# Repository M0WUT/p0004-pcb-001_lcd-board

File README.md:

# P0004-PCB-001 - LCD Board
Front panel board featuring MCU and LCD

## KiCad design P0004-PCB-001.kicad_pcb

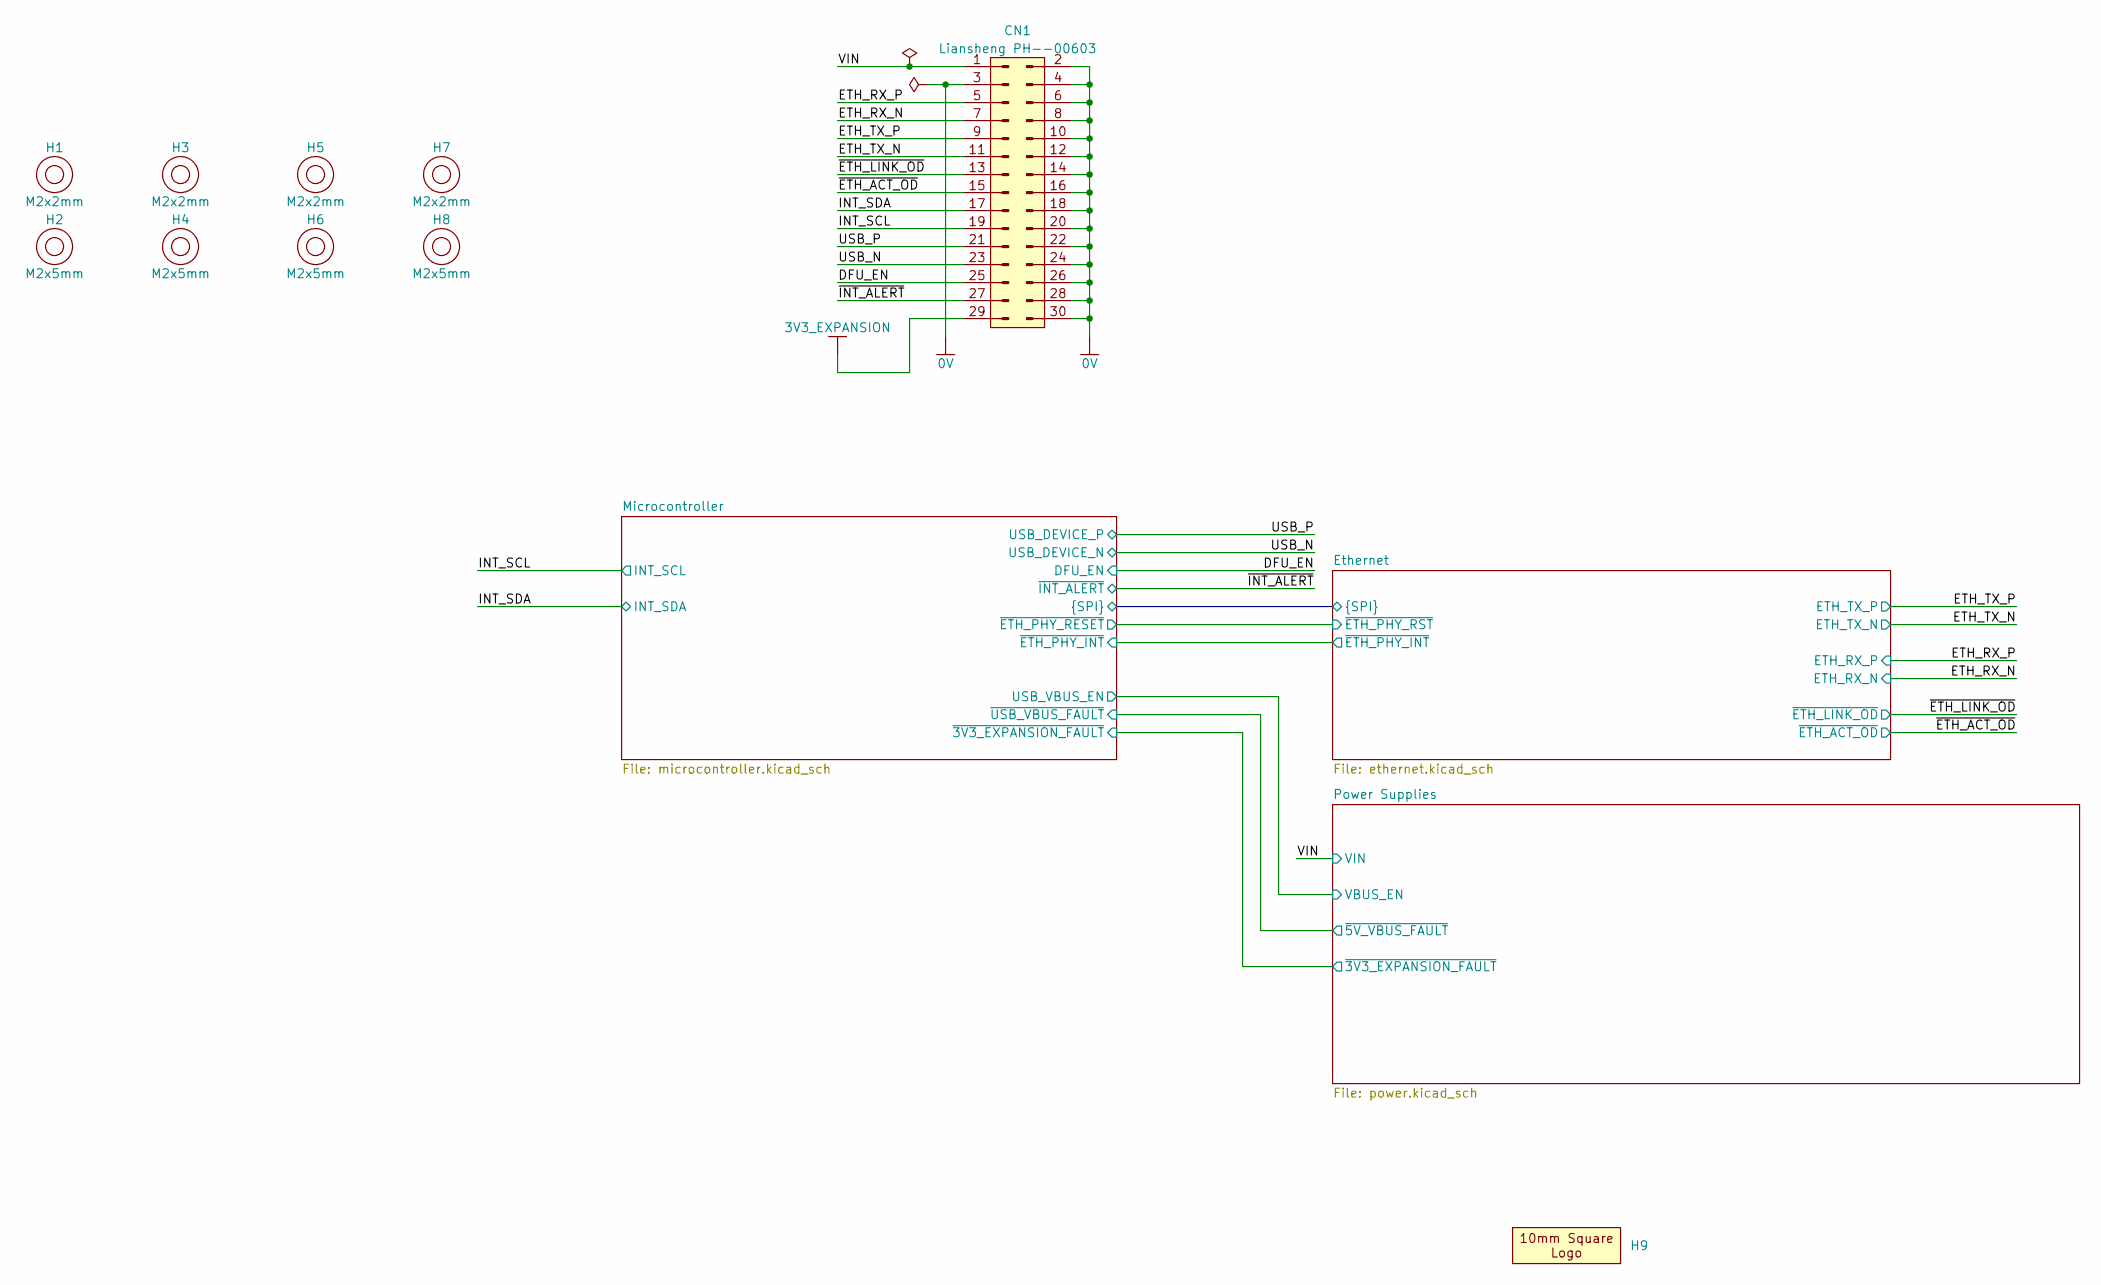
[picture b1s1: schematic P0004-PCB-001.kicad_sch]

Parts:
CN1: Liansheng PH--00603; Liansheng_PH--00603; MPN PH--00603; JLC Part Number C2685170
H1, H3, H5, H7: M2x2mm; Accu_HPS-4-2.2-2-POM-BL; MPN HPS-4-2.2-2-POM-BL
H2, H4, H6, H8: M2x5mm; Accu_HPS-4-2.2-5-POM-BL; MPN HPS-4-2.2-2-POM-BL
H9: Logo_10mmx10mm

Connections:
0V: CN1.2 (Pin_1), CN1.3, CN1.4, CN1.6, CN1.8, CN1.10, CN1.12, CN1.14, CN1.16, CN1.18, CN1.20, CN1.22, CN1.24, CN1.26, CN1.28, CN1.30; also elsewhere on the board
3V3_EXPANSION: CN1.29; also elsewhere on the board
/DFU_EN: CN1.25; also elsewhere on the board
/ETH_RX_N: CN1.7; also elsewhere on the board
/ETH_RX_P: CN1.5; also elsewhere on the board
/ETH_TX_N: CN1.11; also elsewhere on the board
/ETH_TX_P: CN1.9; also elsewhere on the board
/INT_SCL: CN1.19; also elsewhere on the board
/INT_SDA: CN1.17; also elsewhere on the board
/USB_N: CN1.23; also elsewhere on the board
/USB_P: CN1.21; also elsewhere on the board
/VIN: CN1.1; also elsewhere on the board
/~ETH_ACT_OD: CN1.15; also elsewhere on the board
/~ETH_LINK_OD: CN1.13; also elsewhere on the board
/~INT_ALERT: CN1.27; also elsewhere on the board

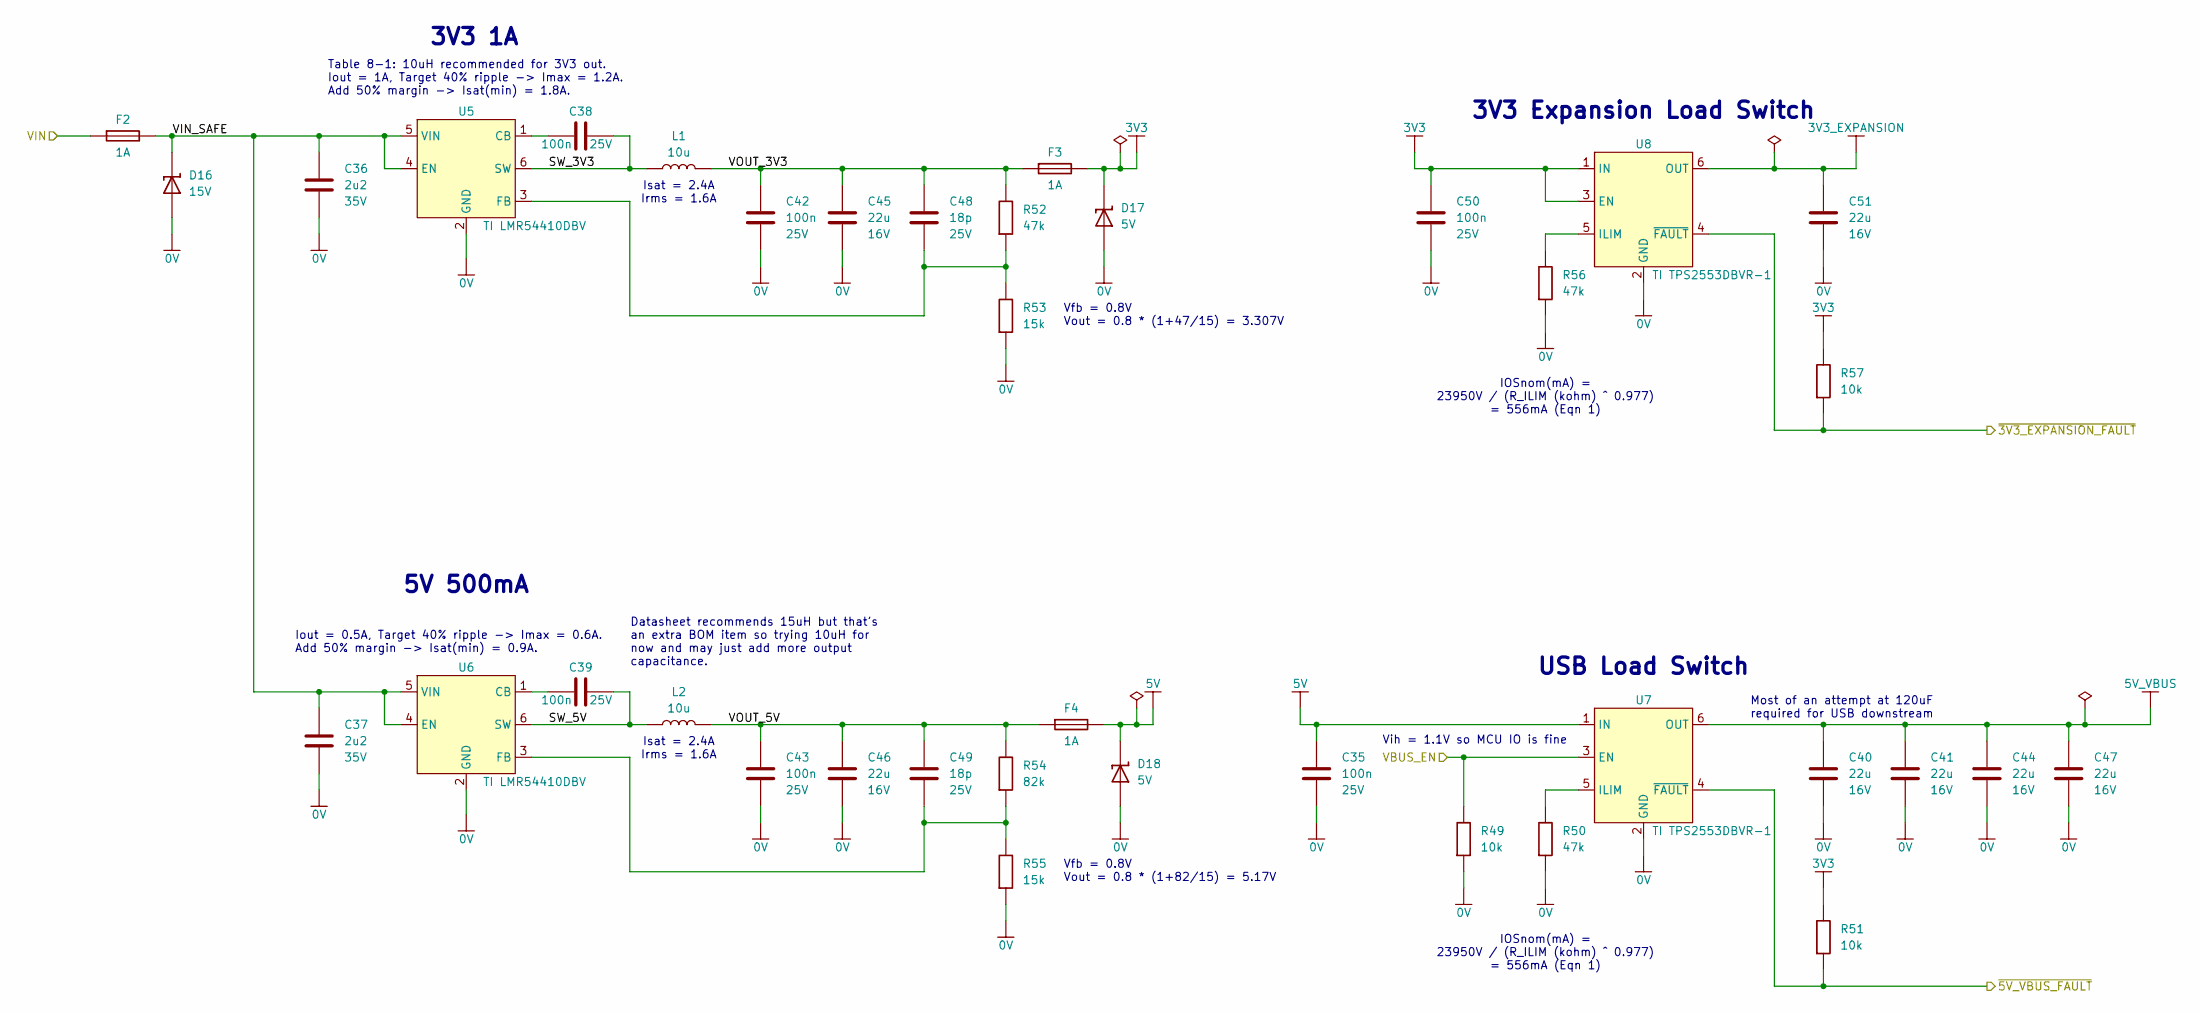
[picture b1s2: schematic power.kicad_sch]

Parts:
C35, C38, C39, C42, C43, C50: 100n; C_0402_1005Metric; Voltage 25V; Tolerance 10%; MPN CC0402KRX7R8BB104
C36, C37: 2u2; C_0402_1005Metric; Voltage 35V; Tolerance 10%; MPN GRM155R6YA225KE11
C40, C41, C44, C45, C46, C47, C51: 22u; C_0603_1608Metric; Voltage 16V; Tolerance 20%; MPN GRM188R61C226ME01
C48, C49: 18p; C_0402_1005Metric; Voltage 25V; Tolerance 10%; MPN C0402C180K3GACTU
D16: 15V; D_SOD-323; MPN CDSOD-323-T15S
D17, D18: 5V; D_SOD-523; MPN H5VND5U
F2, F3, F4: 1A; Fuse_0603_1608Metric; MPN 0467001.NR
L1, L2: 10u; APV_ANR4030; Tolerance 20%; MPN ANR4030T100M
R49, R51, R57: 10k; R_0402_1005Metric; Tolerance 1%; MPN RK73H1ETTP1002F
R50, R52, R56: 47k; R_0402_1005Metric; Tolerance 1%; MPN RK73H1ETTP4702F
R53, R55: 15k; R_0402_1005Metric; Tolerance 1%; MPN RK73H1ETTP1502F
R54: 82k; R_0402_1005Metric; Tolerance 1%; MPN RK73H1ETTP8202F
U5, U6: TI LMR54410DBV; SOT-23-6; MPN LMR54410DBV; JLCPCB Order # C3200265
U7, U8: TI TPS2553DBVR-1; SOT-23-6; MPN TPS2553DBVR-1; JLCPCB Order # C55266

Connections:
0V: C35.2, C36.2, C37.2, C40.2, C41.2, C42.2, C43.2, C44.2, C45.2, C46.2, C47.2, C50.2, C51.2, D16.2 (A), D17.2 (A), D18.2 (A), R49.2, R50.2, R53.2, R55.2, R56.2, U5.2 (GND), U6.2 (GND), U7.2 (GND), U8.2 (GND); also elsewhere on the board
3V3: C50.1, D17.1 (K), F3.2, R51.1, R57.1, U8.1 (IN), U8.3 (EN); also elsewhere on the board
3V3_EXPANSION: C51.1, U8.6 (OUT); also elsewhere on the board
5V: C35.1, D18.1 (K), F4.2, U7.1 (IN)
5V_VBUS: C40.1, C41.1, C44.1, C47.1, U7.6 (OUT); also elsewhere on the board
/Microcontroller/USB_VBUS_EN: R49.1, U7.3 (EN); also elsewhere on the board
/Microcontroller/~3V3_EXPANSION_FAULT: R57.2, U8.4 (~FAULT); also elsewhere on the board
/Microcontroller/~USB_VBUS_FAULT: R51.2, U7.4 (~FAULT); also elsewhere on the board
/Power Supplies/SW_3V3: C38.1, L1.1, U5.6 (SW)
/Power Supplies/SW_5V: C39.1, L2.1, U6.6 (SW)
/Power Supplies/VIN_SAFE: C36.1, C37.1, D16.1 (K), F2.2, U5.4 (EN), U5.5 (VIN), U6.4 (EN), U6.5 (VIN)
/Power Supplies/VOUT_3V3: C42.1, C45.1, C48.1, F3.1, L1.2, R52.1
/Power Supplies/VOUT_5V: C43.1, C46.1, C49.1, F4.1, L2.2, R54.1
/VIN: F2.1; also elsewhere on the board
unnamed: C38.2, U5.1 (CB)
unnamed: C48.2, R52.2, R53.1, U5.3 (FB)
unnamed: C39.2, U6.1 (CB)
unnamed: C49.2, R54.2, R55.1, U6.3 (FB)
unnamed: R50.1, U7.5 (ILIM)
unnamed: R56.1, U8.5 (ILIM)

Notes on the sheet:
3V3 1A
Isat = 2.4A Irms = 1.6A
IOSnom(mA) = 23950V / (R_ILIM (kohm) ^ 0.977) = 556mA (Eqn 1)
Vfb = 0.8V Vout = 0.8 * (1+82/15) = 5.17V
Vih = 1.1V so MCU IO is fine
Table 8-1: 10uH recommended for 3V3 out. Iout = 1A, Target 40% ripple -> Imax = 1.2A. Add 50% margin -> Isat(min) = 1.8A.
USB Load Switch
Most of an attempt at 120uF required for USB downstream
3V3 Expansion Load Switch
Vfb = 0.8V Vout = 0.8 * (1+47/15) = 3.307V
5V 500mA
Datasheet recommends 15uH but that's an extra BOM item so trying 10uH for now and may just add more output capacitance.
Iout = 0.5A, Target 40% ripple -> Imax = 0.6A. Add 50% margin -> Isat(min) = 0.9A.

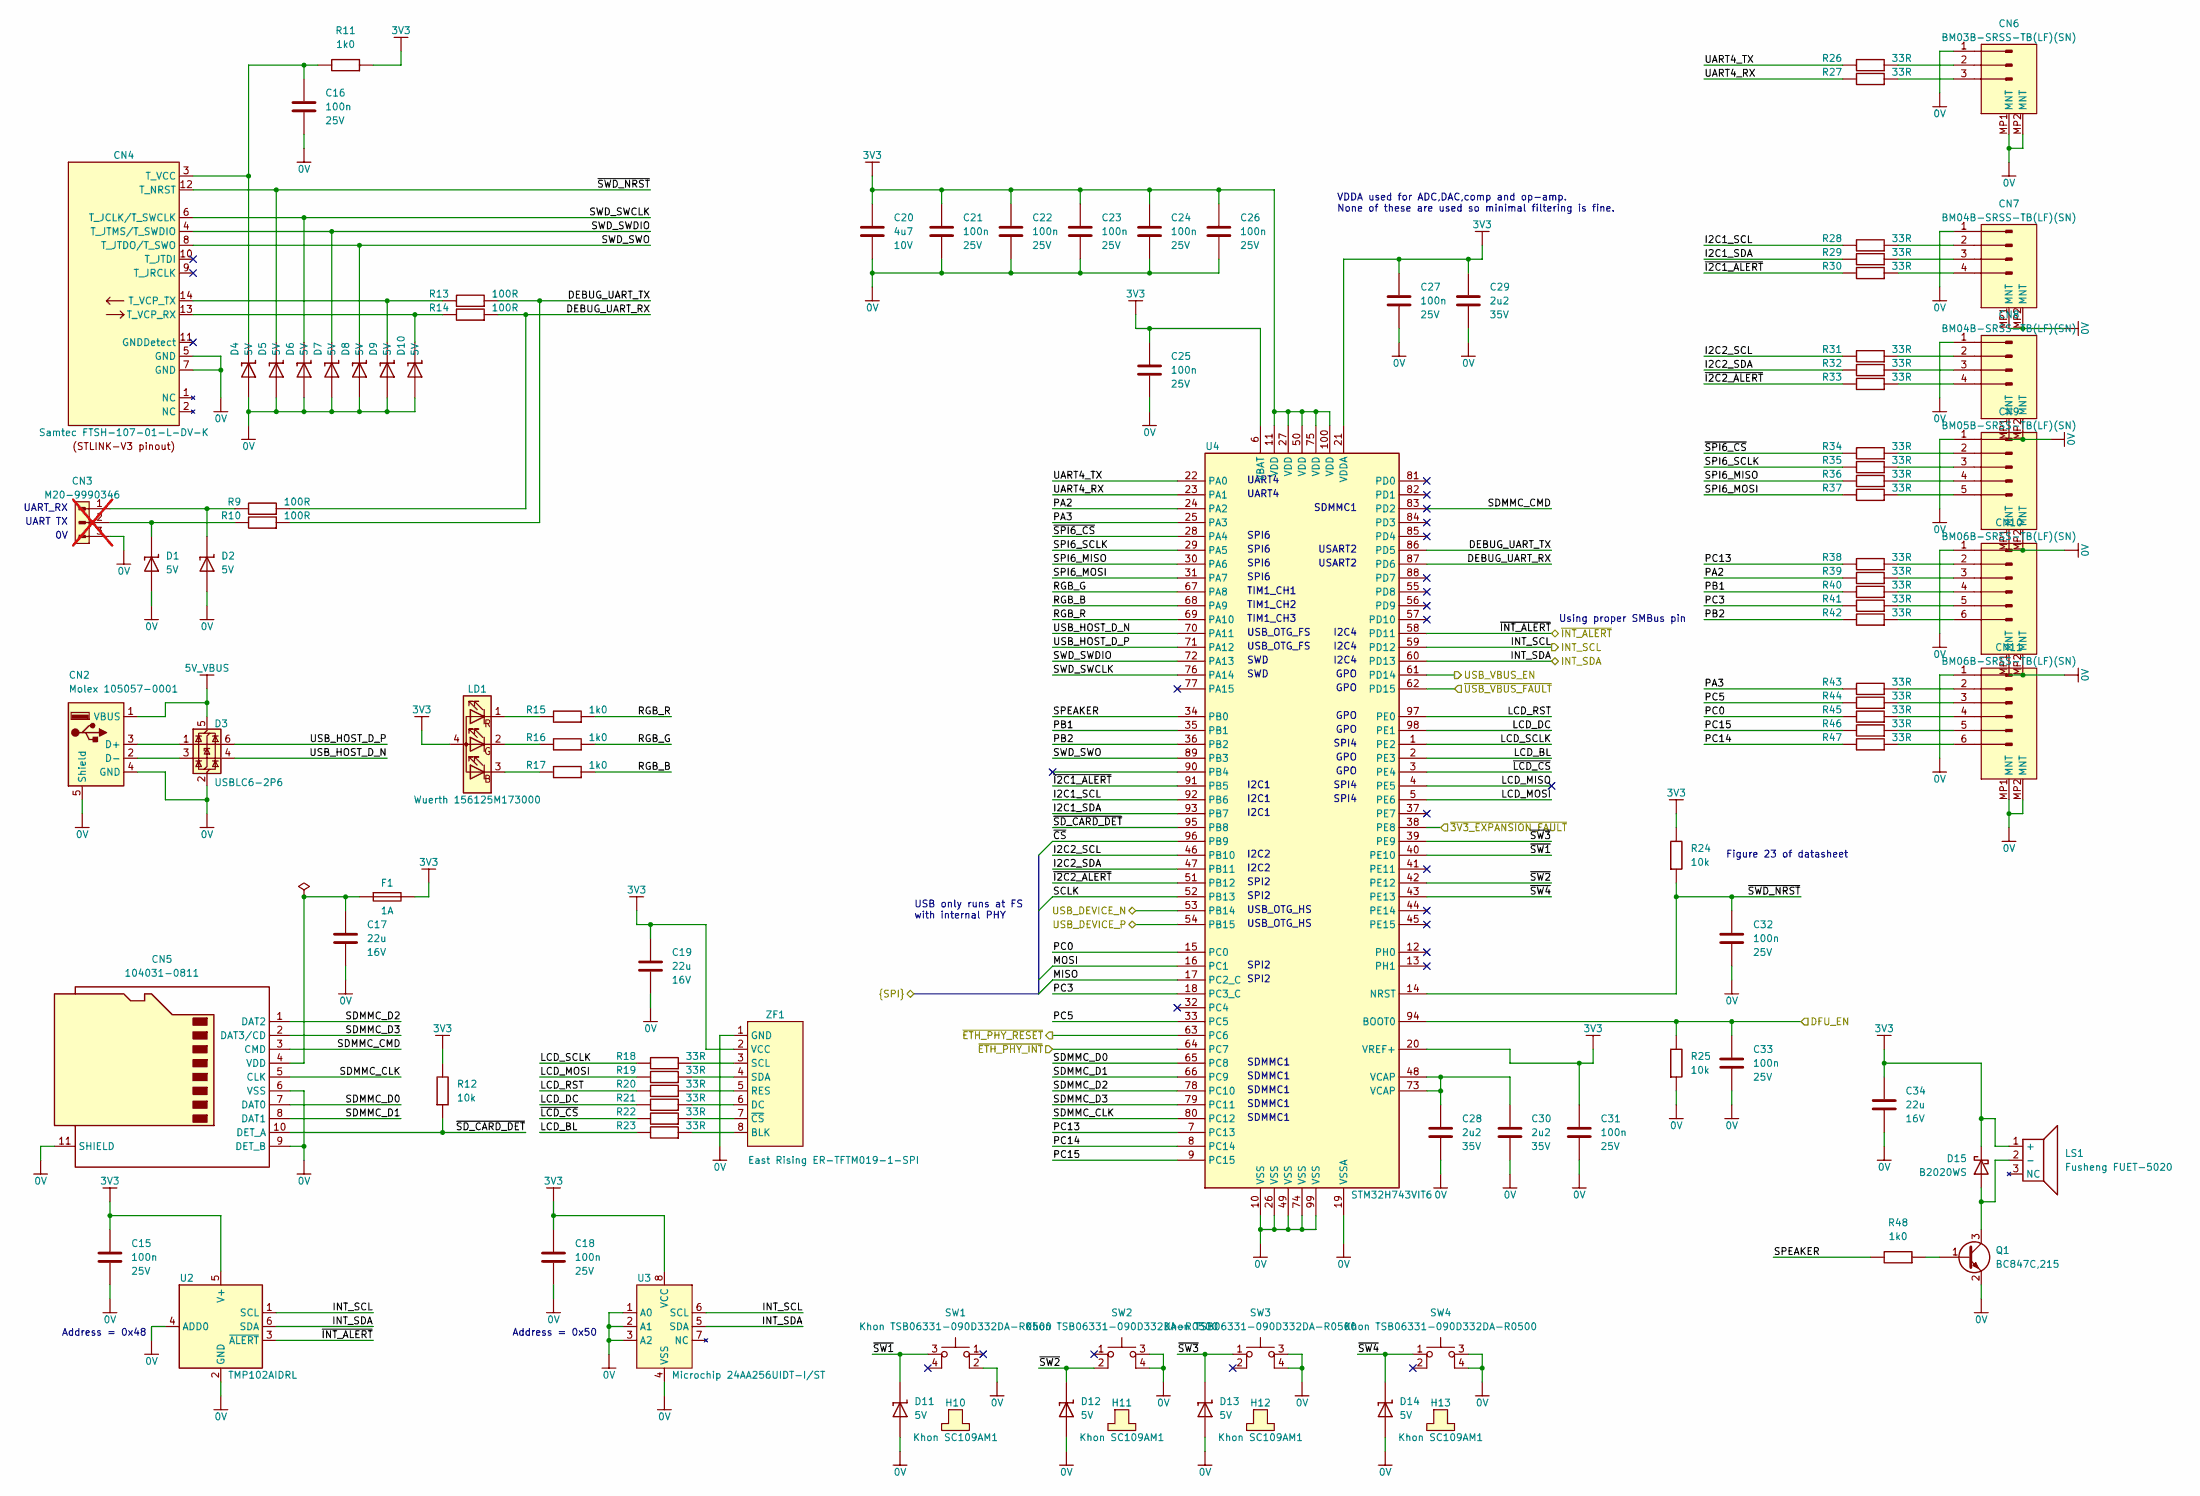
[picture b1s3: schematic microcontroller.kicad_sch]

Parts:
C15, C16, C18, C21, C22, C23, C24, C25, C26, C27, C31, C32, C33: 100n; C_0402_1005Metric; Voltage 25V; Tolerance 10%; MPN CC0402KRX7R8BB104
C17, C19, C34: 22u; C_0603_1608Metric; Voltage 16V; Tolerance 20%; MPN GRM188R61C226ME01
C20: 4u7; C_0402_1005Metric; Voltage 10V; Tolerance 20%; MPN GRM155D71A475ME15
C28, C29, C30: 2u2; C_0402_1005Metric; Voltage 35V; Tolerance 10%; MPN GRM155R6YA225KE11
CN2: Molex 105057-0001; USB-A_Molex_105057-0001_TH_Vertical; MPN 105057-0001
CN3: M20-9990346; MPN M20-9990346; JLCPCB Order # C5355646; not fitted
CN4: Samtec FTSH-107-01-L-DV-K; Header_Samtec_FTSH-107-01-L-DV-K; MPN FTSH-107-01-L-DV-K; JLCPCB Order # C5307809
CN5: 104031-0811; microSD_HC_Molex_104031-0811; MPN 104031-0811
CN6: BM03B-SRSS-TB(LF)(SN); BM03B-SRSS-TB; MPN BM03B-SRSS-TB(LF)(SN); JLCPCB Order # C160389
CN7, CN8: BM04B-SRSS-TB(LF)(SN); BM04B-SRSS-TB; MPN BM04B-SRSS-TB(LF)(SN); JLCPCB Order # C160390
CN9: BM05B-SRSS-TB(LF)(SN); BM05B-SRSS-TB; MPN BM05B-SRSS-TB(LF)(SN); JLCPCB Order # C160391
CN10, CN11: BM06B-SRSS-TB(LF)(SN); BM06B-SRSS-TB; MPN BM06B-SRSS-TB(LF)(SN); JLCPCB Order # C160392
D1, D2, D4, D5, D6, D7, D8, D9, D10, D11, D12, D13, D14: 5V; D_SOD-523; MPN H5VND5U
D3: USBLC6-2P6; SOT-666; MPN USBLC6-2P6
D15: B2020WS; D_SOD-323; MPN B2020WS
F1: 1A; Fuse_0603_1608Metric; MPN 0467001.NR
H10, H11, H12, H13: Khon SC109AM1; Khon_SC109; MPN SC109AM1; JLCPCB Order # C42435457
LD1: Wuerth 156125M173000; Wuerth_156125M173000; MPN 156125M173000; JLCPCB Order # C5341671
LS1: Fusheng FUET-5020; Fusheng_FUET-5020; MPN FUET-5020; JLCPCB Order # C391029
Q1: BC847C,215; SOT-23; MPN BC847C,215; JLCPCB Order # C8664
R9, R10, R13, R14: 100R; R_0402_1005Metric; Tolerance 1%; MPN RK73H1ETTP1000F
R11, R15, R16, R17, R48: 1k0; R_0402_1005Metric; Tolerance 1%; MPN RK73H1ETTP1001F
R12, R24, R25: 10k; R_0402_1005Metric; Tolerance 1%; MPN RK73H1ETTP1002F
R18, R19, R20, R21, R22, R23, R26, R27, R28, R29, R30, R31, R32, R33, R34, R35, R36, R37, R38, R39, R40, R41, R42, R43, R44, R45, R46, R47: 33R; R_0402_1005Metric; Tolerance 1%; MPN RK73H1ETTP33R0F
SW1, SW2, SW3, SW4: Khon TSB06331-090D332DA-R0500; Khon_TSB06331-090; MPN TSB06331-090D332DA-R0500
U2: TMP102AIDRL; SOT-563; MPN TMP102AIDRL; JLCPCB Order # C99269
U3: Microchip 24AA256UIDT-I/ST; TSSOP-8_4.4x3mm_P0.65mm; MPN 24AA256UIDT-I/ST; JLCPCB Order # C619926
U4: STM32H743VIT6; LQFP-100_14x14mm_P0.5mm; MPN STM32H743VIT6; JLCPCB Part # C114409
ZF1: East Rising ER-TFTM019-1-SPI; East-Rising_ER-TFTM019-1-SPI; MPN ER-TFTM019-1-SPI

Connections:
0V: C15.2, C16.2, C17.2, C18.2, C19.2, C20.2, C21.2, C22.2, C23.2, C24.2, C25.2, C26.2, C27.2, C28.2, C29.2, C30.2, C31.2, C32.2, C33.2, C34.2, CN2.4 (GND), CN2.5 (Shield), CN3.3, CN4.5 (GND), CN4.7 (GND), CN5.6 (VSS), CN5.9 (DET_B), CN5.11 (SHIELD), CN6.1, CN6.MP1 (MNT), CN6.MP2 (MNT), CN7.1, CN7.MP1 (MNT), CN7.MP2 (MNT), CN8.1, CN8.MP1 (MNT), CN8.MP2 (MNT), CN9.1, CN9.MP1 (MNT), CN9.MP2 (MNT), CN10.1, CN10.MP1 (MNT), CN10.MP2 (MNT), CN11.1, CN11.MP1 (MNT), CN11.MP2 (MNT), D1.2 (A), D2.2 (A), D3.2 (GND), D4.2 (A), D5.2 (A), D6.2 (A), D7.2 (A), D8.2 (A), D9.2 (A), D10.2 (A), D11.2 (A), D12.2 (A), D13.2 (A), D14.2 (A), Q1.2 (E), R25.2, SW1.2, SW2.3, SW2.4, SW3.3, SW3.4, SW4.3, SW4.4, U2.2 (GND), U2.4 (ADD0), U3.1 (A0), U3.2 (A1), U3.3 (A2), U3.4 (VSS), U4.10 (VSS), U4.19 (VSSA), U4.26 (VSS), U4.49 (VSS), U4.74 (VSS), U4.99 (VSS), ZF1.1 (GND); also elsewhere on the board
3V3: C15.1, C18.1, C19.1, C20.1, C21.1, C22.1, C23.1, C24.1, C25.1, C26.1, C27.1, C29.1, C31.1, C34.1, D15.1 (K), F1.2, LD1.4 (A), LS1.1 (+), R11.2, R12.1, R24.1, U2.5 (V+), U3.8 (VCC), U4.6 (VBAT), U4.11 (VDD), U4.20 (VREF+), U4.21 (VDDA), U4.27 (VDD), U4.50 (VDD), U4.75 (VDD), U4.100 (VDD), ZF1.2 (VCC); also elsewhere on the board
5V_VBUS: CN2.1 (VBUS), D3.5 (VBUS); also elsewhere on the board
/DFU_EN: C33.1, R25.1, U4.94 (BOOT0); also elsewhere on the board
/Ethernet/MISO: U4.17 (PC2_C); also elsewhere on the board
/Ethernet/MOSI: U4.16 (PC1); also elsewhere on the board
/Ethernet/SCLK: U4.52 (PB13); also elsewhere on the board
/Ethernet/~CS: U4.96 (PB9); also elsewhere on the board
/Ethernet/~ETH_PHY_INT: U4.64 (PC7); also elsewhere on the board
/Ethernet/~ETH_PHY_RST: U4.63 (PC6); also elsewhere on the board
/INT_SCL: U2.1 (SCL), U3.6 (SCL), U4.59 (PD12); also elsewhere on the board
/INT_SDA: U2.6 (SDA), U3.5 (SDA), U4.60 (PD13); also elsewhere on the board
/Microcontroller/DEBUG_UART_RX: R9.2, R14.2, U4.87 (PD6)
/Microcontroller/DEBUG_UART_TX: R10.2, R13.2, U4.86 (PD5)
/Microcontroller/I2C1_SCL: R28.1, U4.92 (PB6)
/Microcontroller/I2C1_SDA: R29.1, U4.93 (PB7)
/Microcontroller/I2C2_SCL: R31.1, U4.46 (PB10)
/Microcontroller/I2C2_SDA: R32.1, U4.47 (PB11)
/Microcontroller/LCD_BL: R23.1, U4.2 (PE3)
/Microcontroller/LCD_DC: R21.1, U4.98 (PE1)
/Microcontroller/LCD_MISO: U4.4 (PE5)
/Microcontroller/LCD_MOSI: R19.1, U4.5 (PE6)
/Microcontroller/LCD_RST: R20.1, U4.97 (PE0)
/Microcontroller/LCD_SCLK: R18.1, U4.1 (PE2)
/Microcontroller/PA2: R39.1, U4.24 (PA2)
/Microcontroller/PA3: R43.1, U4.25 (PA3)
/Microcontroller/PB1: R40.1, U4.35 (PB1)
/Microcontroller/PB2: R42.1, U4.36 (PB2)
/Microcontroller/PC0: R45.1, U4.15 (PC0)
/Microcontroller/PC3: R41.1, U4.18 (PC3_C)
/Microcontroller/PC5: R44.1, U4.33 (PC5)
/Microcontroller/PC13: R38.1, U4.7 (PC13)
/Microcontroller/PC14: R47.1, U4.8 (PC14)
/Microcontroller/PC15: R46.1, U4.9 (PC15)
/Microcontroller/RGB_B: R17.2, U4.68 (PA9)
/Microcontroller/RGB_G: R16.2, U4.67 (PA8)
/Microcontroller/RGB_R: R15.2, U4.69 (PA10)
/Microcontroller/SDMMC_CLK: CN5.5 (CLK), U4.80 (PC12)
/Microcontroller/SDMMC_CMD: CN5.3 (CMD), U4.83 (PD2)
/Microcontroller/SDMMC_D0: CN5.7 (DAT0), U4.65 (PC8)
/Microcontroller/SDMMC_D1: CN5.8 (DAT1), U4.66 (PC9)
/Microcontroller/SDMMC_D2: CN5.1 (DAT2), U4.78 (PC10)
/Microcontroller/SDMMC_D3: CN5.2 (DAT3/CD), U4.79 (PC11)
/Microcontroller/SPEAKER: R48.1, U4.34 (PB0)
/Microcontroller/SPI6_MISO: R36.1, U4.30 (PA6)
/Microcontroller/SPI6_MOSI: R37.1, U4.31 (PA7)
/Microcontroller/SPI6_SCLK: R35.1, U4.29 (PA5)
/Microcontroller/SWD_SWCLK: CN4.6 (T_JCLK/T_SWCLK), D6.1 (K), U4.76 (PA14)
/Microcontroller/SWD_SWDIO: CN4.4 (T_JTMS/T_SWDIO), D7.1 (K), U4.72 (PA13)
/Microcontroller/SWD_SWO: CN4.8 (T_JTDO/T_SWO), D8.1 (K), U4.89 (PB3)
/Microcontroller/UART4_RX: R27.1, U4.23 (PA1)
/Microcontroller/UART4_TX: R26.1, U4.22 (PA0)
/Microcontroller/USB_HOST_D_N: D3.4 (I/O2), U4.70 (PA11)
/Microcontroller/USB_HOST_D_P: D3.6 (I/O1), U4.71 (PA12)
/Microcontroller/USB_VBUS_EN: U4.61 (PD14); also elsewhere on the board
/Microcontroller/~3V3_EXPANSION_FAULT: U4.38 (PE8); also elsewhere on the board
/Microcontroller/~I2C1_ALERT: R30.1, U4.91 (PB5)
/Microcontroller/~I2C2_ALERT: R33.1, U4.51 (PB12)
/Microcontroller/~LCD_CS: R22.1, U4.3 (PE4)
/Microcontroller/~SD_CARD_DET: CN5.10 (DET_A), R12.2, U4.95 (PB8)
/Microcontroller/~SPI6_CS: R34.1, U4.28 (PA4)
/Microcontroller/~SW1: D11.1 (K), SW1.3, U4.40 (PE10)
/Microcontroller/~SW2: D12.1 (K), SW2.2, U4.42 (PE12)
/Microcontroller/~SW3: D13.1 (K), SW3.1, U4.39 (PE9)
/Microcontroller/~SW4: D14.1 (K), SW4.1, U4.43 (PE13)
/Microcontroller/~SWD_NRST: C32.1, CN4.12 (T_NRST), D5.1 (K), R24.2, U4.14 (NRST)
/Microcontroller/~USB_VBUS_FAULT: U4.62 (PD15); also elsewhere on the board
/USB_N: U4.53 (PB14); also elsewhere on the board
/USB_P: U4.54 (PB15); also elsewhere on the board
/~INT_ALERT: U2.3 (~ALERT), U4.58 (PD11); also elsewhere on the board
unnamed: C28.1, C30.1, U4.48 (VCAP), U4.73 (VCAP)
unnamed: CN2.3 (D+), D3.1 (I/O1)
unnamed: CN2.2 (D-), D3.3 (I/O2)
unnamed: C16.1, CN4.3 (T_VCC), D4.1 (K), R11.1
unnamed: CN4.13 (T_VCP_RX), D10.1 (K), R14.1
unnamed: CN4.14 (T_VCP_TX), D9.1 (K), R13.1
unnamed: C17.1, CN5.4 (VDD), F1.1
unnamed: CN6.2, R26.2
unnamed: CN6.3, R27.2
unnamed: CN7.2, R28.2
unnamed: CN7.3, R29.2
unnamed: CN7.4, R30.2
unnamed: CN8.2, R31.2
unnamed: CN8.3, R32.2
unnamed: CN8.4, R33.2
unnamed: CN9.2, R34.2
unnamed: CN9.3, R35.2
unnamed: CN9.4, R36.2
unnamed: CN9.5, R37.2
unnamed: CN10.2, R38.2
unnamed: CN10.3, R39.2
unnamed: CN10.4, R40.2
unnamed: CN10.5, R41.2
unnamed: CN10.6, R42.2
unnamed: CN11.2, R43.2
unnamed: CN11.3, R44.2
unnamed: CN11.4, R45.2
unnamed: CN11.5, R46.2
unnamed: CN11.6, R47.2
unnamed: CN3.2, D1.1 (K), R10.1
unnamed: CN3.1, D2.1 (K), R9.1
unnamed: D15.2 (A), LS1.2 (-), Q1.3 (C)
unnamed: LD1.3 (B), R17.1
unnamed: LD1.2 (G), R16.1
unnamed: LD1.1 (R), R15.1
unnamed: Q1.1 (B), R48.2
unnamed: R23.2, ZF1.8 (BLK)
unnamed: R21.2, ZF1.6 (DC)
unnamed: R20.2, ZF1.5 (RES)
unnamed: R18.2, ZF1.3 (SCL)
unnamed: R19.2, ZF1.4 (SDA)
unnamed: R22.2, ZF1.7 (~CS)

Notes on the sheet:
GPO
SDMMC1
SWD
I2C4
TIM1_CH3
VDDA used for ADC,DAC,comp and op-amp. None of these are used so minimal filtering is fine.
USB_OTG_FS
USB only runs at FS with internal PHY
SPI4
SPI6
SPI2
Figure 23 of datasheet
USB_OTG_HS
I2C1
UART TX
USART2
TIM1_CH2
Address = 0x50
UART_RX
Using proper SMBus pin
Address = 0x48
I2C2
TIM1_CH1
UART4

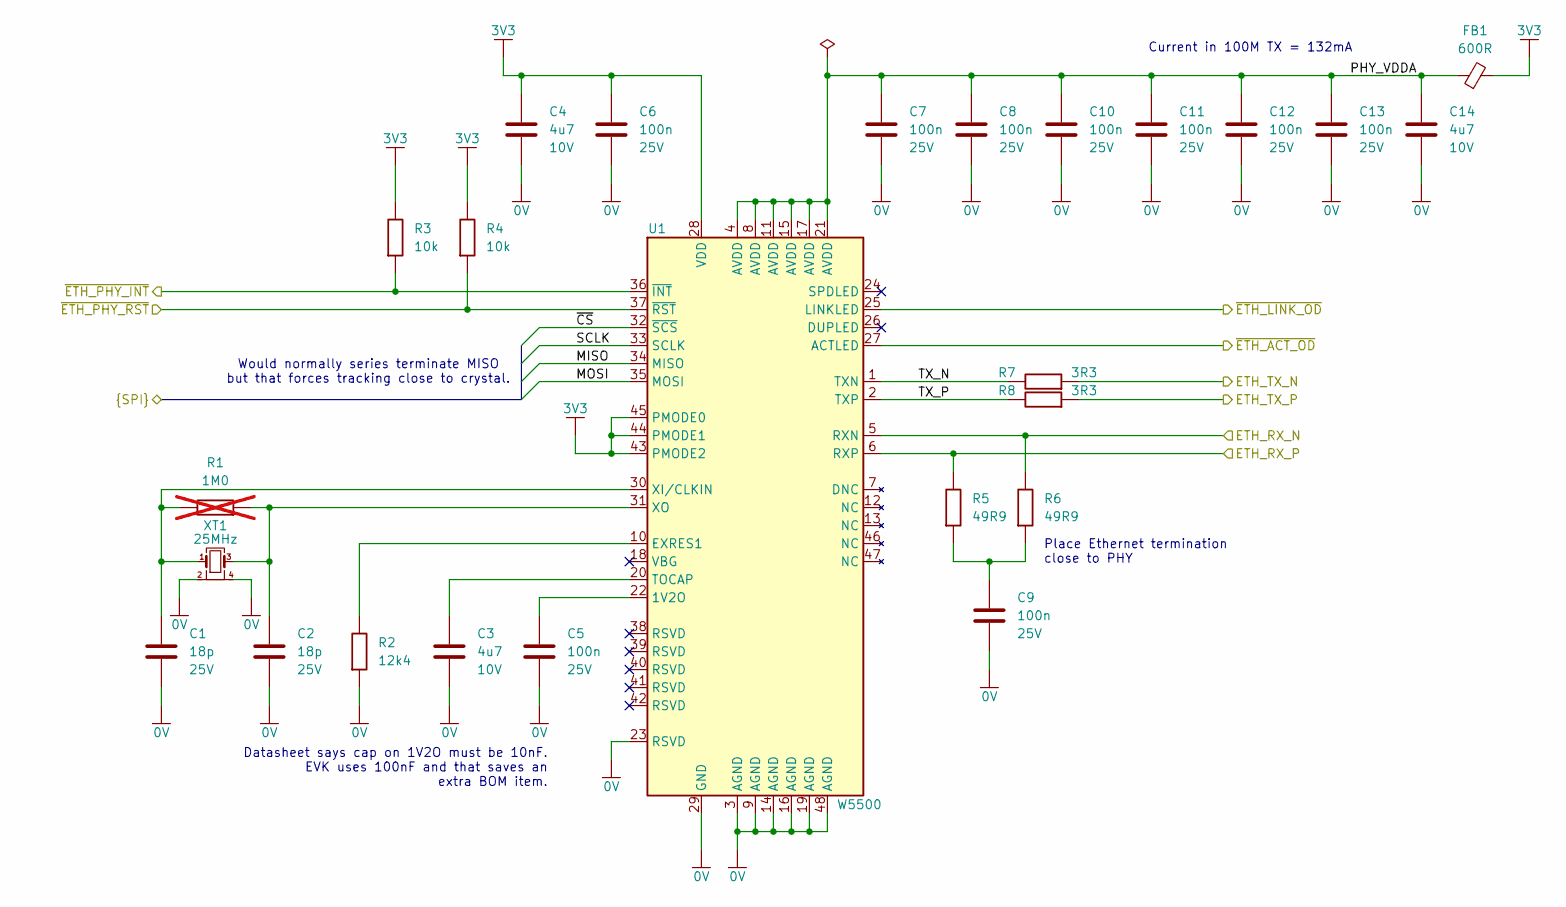
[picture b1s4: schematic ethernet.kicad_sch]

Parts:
C1, C2: 18p; C_0402_1005Metric; Voltage 25V; Tolerance 10%; MPN C0402C180K3GACTU
C3, C4, C14: 4u7; C_0402_1005Metric; Voltage 10V; Tolerance 20%; MPN GRM155D71A475ME15
C5, C6, C7, C8, C9, C10, C11, C12, C13: 100n; C_0402_1005Metric; Voltage 25V; Tolerance 10%; MPN CC0402KRX7R8BB104
FB1: 600R; L_0603_1608Metric; MPN BLM18AG601SN1D
R1: 1M0; R_0402_1005Metric; Tolerance 1%; MPN RK73H1ETTP1004F; not fitted
R2: 12k4; R_0402_1005Metric; Tolerance 1%; MPN RK73H1ETTP1242F
R3, R4: 10k; R_0402_1005Metric; Tolerance 1%; MPN RK73H1ETTP1002F
R5, R6: 49R9; R_0402_1005Metric; Tolerance 1%; MPN RK73H1ETTP49R9F
R7, R8: 3R3; R_0402_1005Metric; Tolerance 1%; MPN RK73H1ETTP3R30F
U1: W5500; LQFP-48_7x7mm_P0.5mm; MPN W5500; JLCPCB Order # C32843
XT1: 25MHz; Murata_XRCGB; MPN XRCGB25M000F3M18R0; JLCPCB Order # C1986195

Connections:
0V: C1.2, C2.2, C3.2, C4.2, C5.2, C6.2, C7.2, C8.2, C9.2, C10.2, C11.2, C12.2, C13.2, C14.2, R2.2, U1.3 (AGND), U1.9 (AGND), U1.14 (AGND), U1.16 (AGND), U1.19 (AGND), U1.23 (RSVD), U1.29 (GND), U1.48 (AGND), XT1.2, XT1.4; also elsewhere on the board
3V3: C4.1, C6.1, FB1.2, R3.1, R4.1, U1.28 (VDD), U1.43 (PMODE2), U1.44 (PMODE1), U1.45 (PMODE0); also elsewhere on the board
/ETH_RX_N: R6.1, U1.5 (RXN); also elsewhere on the board
/ETH_RX_P: R5.1, U1.6 (RXP); also elsewhere on the board
/ETH_TX_N: R7.2; also elsewhere on the board
/ETH_TX_P: R8.2; also elsewhere on the board
/Ethernet/MISO: U1.34 (MISO); also elsewhere on the board
/Ethernet/MOSI: U1.35 (MOSI); also elsewhere on the board
/Ethernet/PHY_VDDA: C7.1, C8.1, C10.1, C11.1, C12.1, C13.1, C14.1, FB1.1, U1.4 (AVDD), U1.8 (AVDD), U1.11 (AVDD), U1.15 (AVDD), U1.17 (AVDD), U1.21 (AVDD)
/Ethernet/SCLK: U1.33 (SCLK); also elsewhere on the board
/Ethernet/TX_N: R7.1, U1.1 (TXN)
/Ethernet/TX_P: R8.1, U1.2 (TXP)
/Ethernet/~CS: U1.32 (~SCS); also elsewhere on the board
/Ethernet/~ETH_PHY_INT: R3.2, U1.36 (~INT); also elsewhere on the board
/Ethernet/~ETH_PHY_RST: R4.2, U1.37 (~RST); also elsewhere on the board
/~ETH_ACT_OD: U1.27 (ACTLED); also elsewhere on the board
/~ETH_LINK_OD: U1.25 (LINKLED); also elsewhere on the board
unnamed: C9.1, R5.2, R6.2
unnamed: C5.1, U1.22 (1V2O)
unnamed: R2.1, U1.10 (EXRES1)
unnamed: C3.1, U1.20 (TOCAP)
unnamed: C1.1, R1.1, U1.30 (XI/CLKIN), XT1.1
unnamed: C2.1, R1.2, U1.31 (XO), XT1.3

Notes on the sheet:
Current in 100M TX = 132mA
Would normally series terminate MISO but that forces tracking close to crystal.
Place Ethernet termination close to PHY
Datasheet says cap on 1V2O must be 10nF. EVK uses 100nF and that saves an extra BOM item.

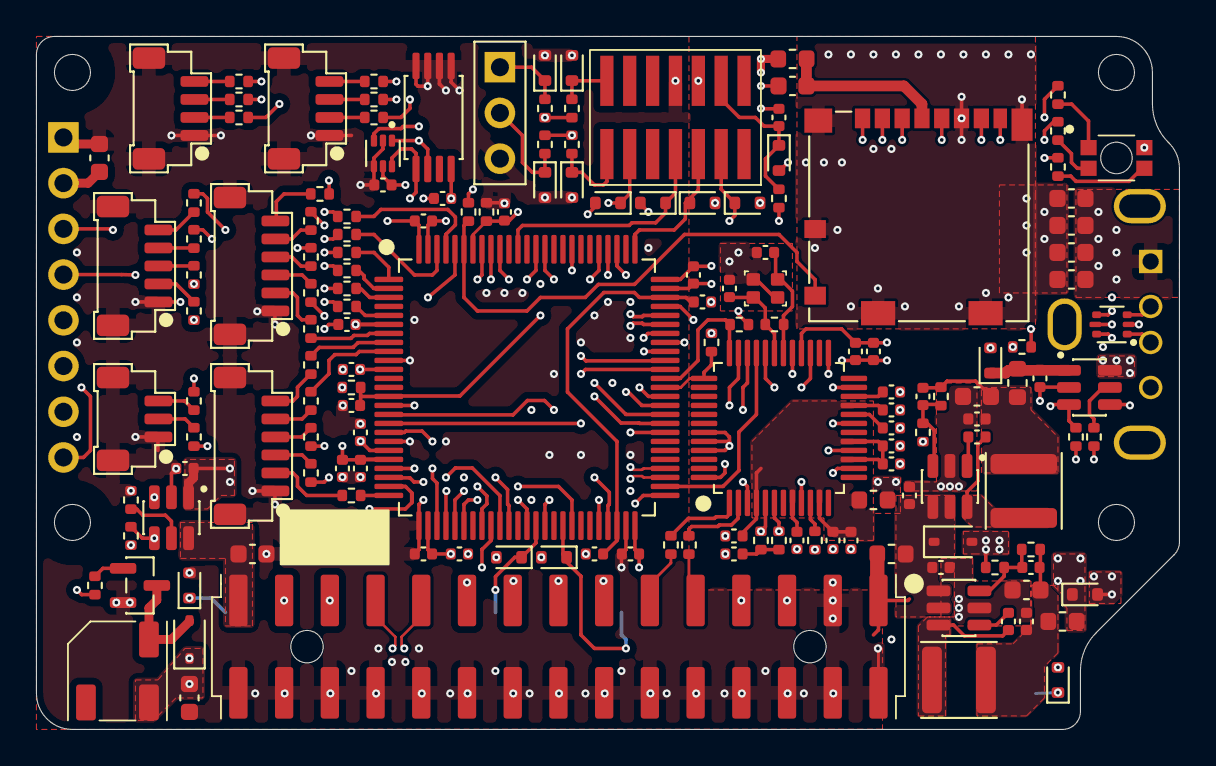
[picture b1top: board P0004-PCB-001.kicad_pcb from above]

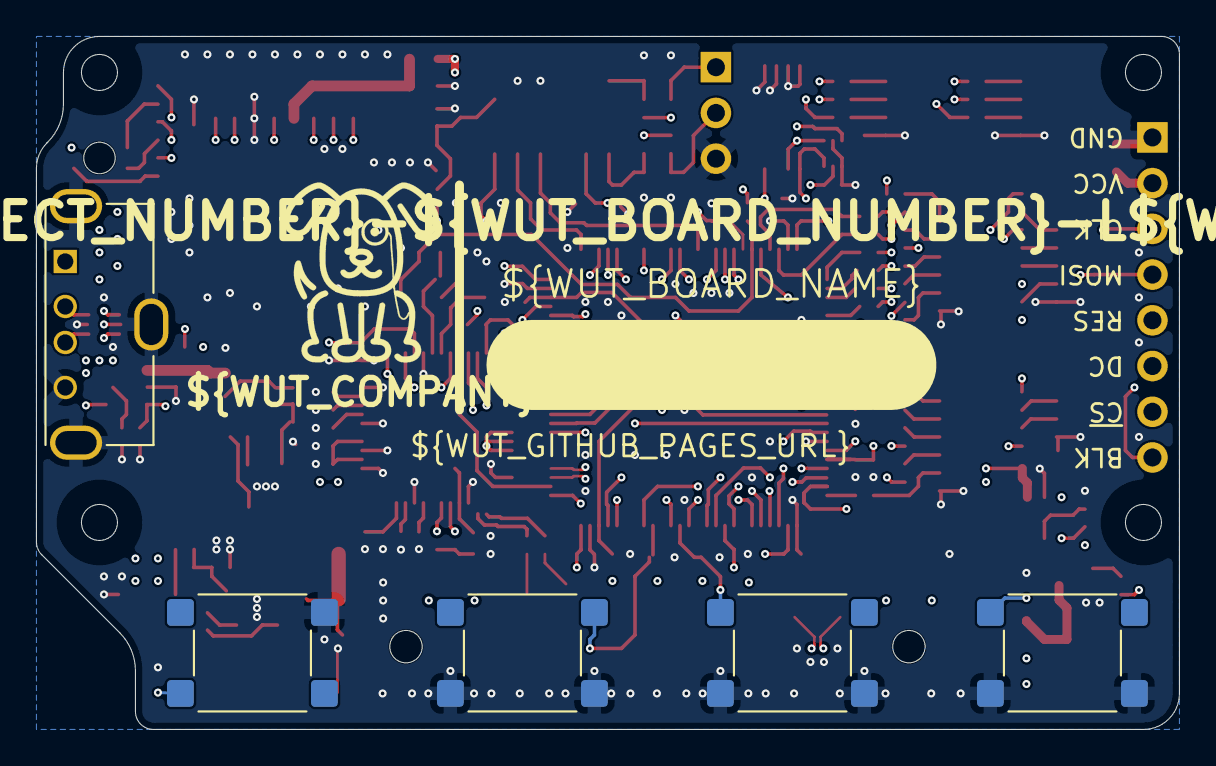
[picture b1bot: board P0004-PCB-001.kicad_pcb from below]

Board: 6 copper layers, 63.5 x 38.5 mm, 174 parts (19 on the bottom side), 140 nets.

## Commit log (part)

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2026-06-06 Argonaut: Created
2026-06-06 started adding components
2026-06-07 testing ci config
2026-06-07 started on DCDC section
2026-06-08 added ethernet phy
2026-06-09 started on mcu pinout
2026-06-12 layout progress
2026-06-13 added 5v regulator
2026-06-14 helps if you save first
2026-06-17 did a few little bits on layout
2026-06-18 more progress
2026-06-20 most things connected
2026-06-21 headers now connected
